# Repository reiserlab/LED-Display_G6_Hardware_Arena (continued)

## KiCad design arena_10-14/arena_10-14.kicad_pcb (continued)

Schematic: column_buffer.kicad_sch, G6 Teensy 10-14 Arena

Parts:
C44, C45, C46, C47: 0.1uF; C_0402_1005Metric; LCSC Part # C1525
R109, R110, R111, R112, R113, R114, R115, R116: 33; R_0402_1005Metric; LCSC Part # C25105
U42, U43, U44, U45: 74LVC2G17; SOT-23-6; LCSC Part # C7394037

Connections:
+3.3V: C44.1, C45.1, C46.1, C47.1, U42.5 (VCC), U43.5 (VCC), U44.5 (VCC), U45.5 (VCC); also elsewhere on the board
/Fan Out/PAN.CIPO_B0_P1: R109.2; also elsewhere on the board
/Fan Out/PAN.COPI_B0_P1: U43.3; also elsewhere on the board
/Fan Out/PAN.CS_00_P1: U42.3; also elsewhere on the board
/Fan Out/PAN.CS_01_P1: U44.1; also elsewhere on the board
/Fan Out/PAN.CS_02_P1: U44.3; also elsewhere on the board
/Fan Out/PAN.CS_03_P1: U45.1; also elsewhere on the board
/Fan Out/PAN.EINT_P1: U45.3; also elsewhere on the board
/Fan Out/PAN.SCK_B0_P1: U43.1; also elsewhere on the board
/Panels/Panel Column P1/Column Buffer/CIPO_IN: U42.1; also elsewhere on the board
/Panels/Panel Column P1/Column Buffer/COPI_OUT: R111.2; also elsewhere on the board
/Panels/Panel Column P1/Column Buffer/CS0_OUT: R112.2; also elsewhere on the board
/Panels/Panel Column P1/Column Buffer/CS1_OUT: R113.2; also elsewhere on the board
/Panels/Panel Column P1/Column Buffer/CS2_OUT: R114.2; also elsewhere on the board
/Panels/Panel Column P1/Column Buffer/CS_3OUT: R115.2; also elsewhere on the board
/Panels/Panel Column P1/Column Buffer/EINT_OUT: R116.2; also elsewhere on the board
/Panels/Panel Column P1/Column Buffer/SCK_OUT: R110.2; also elsewhere on the board
GND: C44.2, C45.2, C46.2, C47.2, U42.2 (GND), U43.2 (GND), U44.2 (GND), U45.2 (GND); also elsewhere on the board
unnamed: R109.1, U42.6
unnamed: R110.1, U43.6
unnamed: R111.1, U43.4
unnamed: R112.1, U42.4
unnamed: R113.1, U44.6
unnamed: R114.1, U44.4
unnamed: R115.1, U45.6
unnamed: R116.1, U45.4

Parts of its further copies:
C50, C51, C52, C53, C55, C56, C57, C58, C60, C61, C62, C63, C65, C66, C67, C68, C70, C71, C72, C73, C75, C76, C77, C78, C80, C81, C82, C83, C85, C86, C87, C88, C153, C154, C155, C156: 0.1uF; C_0402_1005Metric; LCSC Part # C1525
R117, R118, R119, R120, R121, R122, R123, R124, R125, R126, R127, R128, R129, R130, R131, R132, R133, R134, R135, R136, R137, R138, R139, R140, R141, R142, R143, R144, R145, R146, R147, R148, R149, R150, R151, R152, R153, R154, R155, R156, R157, R158, R159, R160, R161, R162, R163, R164, R165, R166, R167, R168, R169, R170, R171, R172, R173, R174, R175, R176, R177, R178, R179, R180, R241, R242, R243, R244, R245, R246, R247, R248: 33; R_0402_1005Metric; LCSC Part # C25105
U46, U47, U48, U49, U50, U51, U52, U53, U54, U55, U56, U57, U58, U59, U60, U61, U62, U63, U64, U65, U66, U67, U68, U69, U70, U71, U72, U73, U74, U75, U76, U77, U128, U129, U130, U131: 74LVC2G17; SOT-23-6; LCSC Part # C7394037

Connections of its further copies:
+3.3V: C50.1, C51.1, C52.1, C53.1, C55.1, C56.1, C57.1, C58.1, C60.1, C61.1, C62.1, C63.1, C65.1, C66.1, C67.1, C68.1, C70.1, C71.1, C72.1, C73.1, C75.1, C76.1, C77.1, C78.1, C80.1, C81.1, C82.1, C83.1, C85.1, C86.1, C87.1, C88.1, C153.1, C154.1, C155.1, C156.1, U46.5 (VCC), U47.5 (VCC), U48.5 (VCC), U49.5 (VCC), U50.5 (VCC), U51.5 (VCC), U52.5 (VCC), U53.5 (VCC), U54.5 (VCC), U55.5 (VCC), U56.5 (VCC), U57.5 (VCC), U58.5 (VCC), U59.5 (VCC), U60.5 (VCC), U61.5 (VCC), U62.5 (VCC), U63.5 (VCC), U64.5 (VCC), U65.5 (VCC), U66.5 (VCC), U67.5 (VCC), U68.5 (VCC), U69.5 (VCC), U70.5 (VCC), U71.5 (VCC), U72.5 (VCC), U73.5 (VCC), U74.5 (VCC), U75.5 (VCC), U76.5 (VCC), U77.5 (VCC), U128.5 (VCC), U129.5 (VCC), U130.5 (VCC), U131.5 (VCC); also elsewhere on the board
/Fan Out/PAN.CIPO_B0_P2: R117.2; also elsewhere on the board
/Fan Out/PAN.CIPO_B0_P3: R125.2; also elsewhere on the board
/Fan Out/PAN.CIPO_B0_P4: R133.2; also elsewhere on the board
/Fan Out/PAN.CIPO_B0_P5: R141.2; also elsewhere on the board
/Fan Out/PAN.CIPO_B1_P6: R241.2; also elsewhere on the board
/Fan Out/PAN.CIPO_B1_P7: R149.2; also elsewhere on the board
/Fan Out/PAN.CIPO_B1_P8: R157.2; also elsewhere on the board
/Fan Out/PAN.CIPO_B1_P9: R165.2; also elsewhere on the board
/Fan Out/PAN.CIPO_B1_P10: R173.2; also elsewhere on the board
/Fan Out/PAN.COPI_B0_P2: U47.3; also elsewhere on the board
/Fan Out/PAN.COPI_B0_P3: U51.3; also elsewhere on the board
/Fan Out/PAN.COPI_B0_P4: U55.3; also elsewhere on the board
/Fan Out/PAN.COPI_B0_P5: U59.3; also elsewhere on the board
/Fan Out/PAN.COPI_B1_P6: U129.3; also elsewhere on the board
/Fan Out/PAN.COPI_B1_P7: U63.3; also elsewhere on the board
/Fan Out/PAN.COPI_B1_P8: U67.3; also elsewhere on the board
/Fan Out/PAN.COPI_B1_P9: U71.3; also elsewhere on the board
/Fan Out/PAN.COPI_B1_P10: U75.3; also elsewhere on the board
/Fan Out/PAN.CS_00_P6: U128.3; also elsewhere on the board
/Fan Out/PAN.CS_01_P6: U130.1; also elsewhere on the board
/Fan Out/PAN.CS_02_P6: U130.3; also elsewhere on the board
/Fan Out/PAN.CS_03_P6: U131.1; also elsewhere on the board
/Fan Out/PAN.CS_04_P2: U46.3; also elsewhere on the board
/Fan Out/PAN.CS_04_P7: U62.3; also elsewhere on the board
/Fan Out/PAN.CS_05_P2: U48.1; also elsewhere on the board
/Fan Out/PAN.CS_05_P7: U64.1; also elsewhere on the board
/Fan Out/PAN.CS_06_P2: U48.3; also elsewhere on the board
/Fan Out/PAN.CS_06_P7: U64.3; also elsewhere on the board
/Fan Out/PAN.CS_07_P2: U49.1; also elsewhere on the board
/Fan Out/PAN.CS_07_P7: U65.1; also elsewhere on the board
/Fan Out/PAN.CS_08_P3: U50.3; also elsewhere on the board
/Fan Out/PAN.CS_08_P8: U66.3; also elsewhere on the board
/Fan Out/PAN.CS_09_P3: U52.1; also elsewhere on the board
/Fan Out/PAN.CS_09_P8: U68.1; also elsewhere on the board
/Fan Out/PAN.CS_10_P3: U52.3; also elsewhere on the board
/Fan Out/PAN.CS_10_P8: U68.3; also elsewhere on the board
/Fan Out/PAN.CS_11_P3: U53.1; also elsewhere on the board
/Fan Out/PAN.CS_11_P8: U69.1; also elsewhere on the board
/Fan Out/PAN.CS_12_P4: U54.3; also elsewhere on the board
/Fan Out/PAN.CS_12_P9: U70.3; also elsewhere on the board
/Fan Out/PAN.CS_13_P4: U56.1; also elsewhere on the board
/Fan Out/PAN.CS_13_P9: U72.1; also elsewhere on the board
/Fan Out/PAN.CS_14_P4: U56.3; also elsewhere on the board
/Fan Out/PAN.CS_14_P9: U72.3; also elsewhere on the board
/Fan Out/PAN.CS_15_P4: U57.1; also elsewhere on the board
/Fan Out/PAN.CS_15_P9: U73.1; also elsewhere on the board
/Fan Out/PAN.CS_16_P5: U58.3; also elsewhere on the board
/Fan Out/PAN.CS_16_P10: U74.3; also elsewhere on the board
/Fan Out/PAN.CS_17_P5: U60.1; also elsewhere on the board
/Fan Out/PAN.CS_17_P10: U76.1; also elsewhere on the board
/Fan Out/PAN.CS_18_P5: U60.3; also elsewhere on the board
/Fan Out/PAN.CS_18_P10: U76.3; also elsewhere on the board
/Fan Out/PAN.CS_19_P5: U61.1; also elsewhere on the board
/Fan Out/PAN.CS_19_P10: U77.1; also elsewhere on the board
/Fan Out/PAN.EINT_P2: U49.3; also elsewhere on the board
/Fan Out/PAN.EINT_P3: U53.3; also elsewhere on the board
/Fan Out/PAN.EINT_P4: U57.3; also elsewhere on the board
/Fan Out/PAN.EINT_P5: U61.3; also elsewhere on the board
/Fan Out/PAN.EINT_P6: U131.3; also elsewhere on the board
/Fan Out/PAN.EINT_P7: U65.3; also elsewhere on the board
/Fan Out/PAN.EINT_P8: U69.3; also elsewhere on the board
/Fan Out/PAN.EINT_P9: U73.3; also elsewhere on the board
/Fan Out/PAN.EINT_P10: U77.3; also elsewhere on the board
/Fan Out/PAN.SCK_B0_P2: U47.1; also elsewhere on the board
/Fan Out/PAN.SCK_B0_P3: U51.1; also elsewhere on the board
/Fan Out/PAN.SCK_B0_P4: U55.1; also elsewhere on the board
/Fan Out/PAN.SCK_B0_P5: U59.1; also elsewhere on the board
/Fan Out/PAN.SCK_B1_P6: U129.1; also elsewhere on the board
/Fan Out/PAN.SCK_B1_P7: U63.1; also elsewhere on the board
/Fan Out/PAN.SCK_B1_P8: U67.1; also elsewhere on the board
/Fan Out/PAN.SCK_B1_P9: U71.1; also elsewhere on the board
/Fan Out/PAN.SCK_B1_P10: U75.1; also elsewhere on the board
/Panels/Panel Column P2/Column Buffer/CIPO_IN: U46.1; also elsewhere on the board
/Panels/Panel Column P2/Column Buffer/COPI_OUT: R119.2; also elsewhere on the board
/Panels/Panel Column P2/Column Buffer/CS0_OUT: R120.2; also elsewhere on the board
/Panels/Panel Column P2/Column Buffer/CS1_OUT: R121.2; also elsewhere on the board
/Panels/Panel Column P2/Column Buffer/CS2_OUT: R122.2; also elsewhere on the board
/Panels/Panel Column P2/Column Buffer/CS_3OUT: R123.2; also elsewhere on the board
/Panels/Panel Column P2/Column Buffer/EINT_OUT: R124.2; also elsewhere on the board
/Panels/Panel Column P2/Column Buffer/SCK_OUT: R118.2; also elsewhere on the board
/Panels/Panel Column P3/Column Buffer/CIPO_IN: U50.1; also elsewhere on the board
/Panels/Panel Column P3/Column Buffer/COPI_OUT: R127.2; also elsewhere on the board
/Panels/Panel Column P3/Column Buffer/CS0_OUT: R128.2; also elsewhere on the board
/Panels/Panel Column P3/Column Buffer/CS1_OUT: R129.2; also elsewhere on the board
/Panels/Panel Column P3/Column Buffer/CS2_OUT: R130.2; also elsewhere on the board
/Panels/Panel Column P3/Column Buffer/CS_3OUT: R131.2; also elsewhere on the board
/Panels/Panel Column P3/Column Buffer/EINT_OUT: R132.2; also elsewhere on the board
/Panels/Panel Column P3/Column Buffer/SCK_OUT: R126.2; also elsewhere on the board
/Panels/Panel Column P4/Column Buffer/CIPO_IN: U54.1; also elsewhere on the board
/Panels/Panel Column P4/Column Buffer/COPI_OUT: R135.2; also elsewhere on the board
/Panels/Panel Column P4/Column Buffer/CS0_OUT: R136.2; also elsewhere on the board
/Panels/Panel Column P4/Column Buffer/CS1_OUT: R137.2; also elsewhere on the board
/Panels/Panel Column P4/Column Buffer/CS2_OUT: R138.2; also elsewhere on the board
/Panels/Panel Column P4/Column Buffer/CS_3OUT: R139.2; also elsewhere on the board
/Panels/Panel Column P4/Column Buffer/EINT_OUT: R140.2; also elsewhere on the board
/Panels/Panel Column P4/Column Buffer/SCK_OUT: R134.2; also elsewhere on the board
/Panels/Panel Column P5/Column Buffer/CIPO_IN: U58.1; also elsewhere on the board
/Panels/Panel Column P5/Column Buffer/COPI_OUT: R143.2; also elsewhere on the board
/Panels/Panel Column P5/Column Buffer/CS0_OUT: R144.2; also elsewhere on the board
/Panels/Panel Column P5/Column Buffer/CS1_OUT: R145.2; also elsewhere on the board
/Panels/Panel Column P5/Column Buffer/CS2_OUT: R146.2; also elsewhere on the board
/Panels/Panel Column P5/Column Buffer/CS_3OUT: R147.2; also elsewhere on the board
/Panels/Panel Column P5/Column Buffer/EINT_OUT: R148.2; also elsewhere on the board
/Panels/Panel Column P5/Column Buffer/SCK_OUT: R142.2; also elsewhere on the board
/Panels/Panel Column P6/Column Buffer/CIPO_IN: U128.1; also elsewhere on the board
/Panels/Panel Column P6/Column Buffer/COPI_OUT: R243.2; also elsewhere on the board
/Panels/Panel Column P6/Column Buffer/CS0_OUT: R244.2; also elsewhere on the board
/Panels/Panel Column P6/Column Buffer/CS1_OUT: R245.2; also elsewhere on the board
/Panels/Panel Column P6/Column Buffer/CS2_OUT: R246.2; also elsewhere on the board
/Panels/Panel Column P6/Column Buffer/CS_3OUT: R247.2; also elsewhere on the board
/Panels/Panel Column P6/Column Buffer/EINT_OUT: R248.2; also elsewhere on the board
/Panels/Panel Column P6/Column Buffer/SCK_OUT: R242.2; also elsewhere on the board
/Panels/Panel Column P7/Column Buffer/CIPO_IN: U62.1; also elsewhere on the board
/Panels/Panel Column P7/Column Buffer/COPI_OUT: R151.2; also elsewhere on the board
/Panels/Panel Column P7/Column Buffer/CS0_OUT: R152.2; also elsewhere on the board
/Panels/Panel Column P7/Column Buffer/CS1_OUT: R153.2; also elsewhere on the board
/Panels/Panel Column P7/Column Buffer/CS2_OUT: R154.2; also elsewhere on the board
/Panels/Panel Column P7/Column Buffer/CS_3OUT: R155.2; also elsewhere on the board
/Panels/Panel Column P7/Column Buffer/EINT_OUT: R156.2; also elsewhere on the board
/Panels/Panel Column P7/Column Buffer/SCK_OUT: R150.2; also elsewhere on the board
/Panels/Panel Column P8/Column Buffer/CIPO_IN: U66.1; also elsewhere on the board
/Panels/Panel Column P8/Column Buffer/COPI_OUT: R159.2; also elsewhere on the board
/Panels/Panel Column P8/Column Buffer/CS0_OUT: R160.2; also elsewhere on the board
/Panels/Panel Column P8/Column Buffer/CS1_OUT: R161.2; also elsewhere on the board
/Panels/Panel Column P8/Column Buffer/CS2_OUT: R162.2; also elsewhere on the board
/Panels/Panel Column P8/Column Buffer/CS_3OUT: R163.2; also elsewhere on the board
/Panels/Panel Column P8/Column Buffer/EINT_OUT: R164.2; also elsewhere on the board
/Panels/Panel Column P8/Column Buffer/SCK_OUT: R158.2; also elsewhere on the board
/Panels/Panel Column P9/Column Buffer/CIPO_IN: U70.1; also elsewhere on the board
/Panels/Panel Column P9/Column Buffer/COPI_OUT: R167.2; also elsewhere on the board
/Panels/Panel Column P9/Column Buffer/CS0_OUT: R168.2; also elsewhere on the board
/Panels/Panel Column P9/Column Buffer/CS1_OUT: R169.2; also elsewhere on the board
/Panels/Panel Column P9/Column Buffer/CS2_OUT: R170.2; also elsewhere on the board
/Panels/Panel Column P9/Column Buffer/CS_3OUT: R171.2; also elsewhere on the board
/Panels/Panel Column P9/Column Buffer/EINT_OUT: R172.2; also elsewhere on the board
/Panels/Panel Column P9/Column Buffer/SCK_OUT: R166.2; also elsewhere on the board
/Panels/Panel Column P10/Column Buffer/CIPO_IN: U74.1; also elsewhere on the board
/Panels/Panel Column P10/Column Buffer/COPI_OUT: R175.2; also elsewhere on the board
/Panels/Panel Column P10/Column Buffer/CS0_OUT: R176.2; also elsewhere on the board
/Panels/Panel Column P10/Column Buffer/CS1_OUT: R177.2; also elsewhere on the board
/Panels/Panel Column P10/Column Buffer/CS2_OUT: R178.2; also elsewhere on the board
/Panels/Panel Column P10/Column Buffer/CS_3OUT: R179.2; also elsewhere on the board
/Panels/Panel Column P10/Column Buffer/EINT_OUT: R180.2; also elsewhere on the board
/Panels/Panel Column P10/Column Buffer/SCK_OUT: R174.2; also elsewhere on the board
GND: C50.2, C51.2, C52.2, C53.2, C55.2, C56.2, C57.2, C58.2, C60.2, C61.2, C62.2, C63.2, C65.2, C66.2, C67.2, C68.2, C70.2, C71.2, C72.2, C73.2, C75.2, C76.2, C77.2, C78.2, C80.2, C81.2, C82.2, C83.2, C85.2, C86.2, C87.2, C88.2, C153.2, C154.2, C155.2, C156.2, U46.2 (GND), U47.2 (GND), U48.2 (GND), U49.2 (GND), U50.2 (GND), U51.2 (GND), U52.2 (GND), U53.2 (GND), U54.2 (GND), U55.2 (GND), U56.2 (GND), U57.2 (GND), U58.2 (GND), U59.2 (GND), U60.2 (GND), U61.2 (GND), U62.2 (GND), U63.2 (GND), U64.2 (GND), U65.2 (GND), U66.2 (GND), U67.2 (GND), U68.2 (GND), U69.2 (GND), U70.2 (GND), U71.2 (GND), U72.2 (GND), U73.2 (GND), U74.2 (GND), U75.2 (GND), U76.2 (GND), U77.2 (GND), U128.2 (GND), U129.2 (GND), U130.2 (GND), U131.2 (GND); also elsewhere on the board
unnamed: R117.1, U46.6
unnamed: R118.1, U47.6
unnamed: R119.1, U47.4
unnamed: R120.1, U46.4
unnamed: R121.1, U48.6
unnamed: R122.1, U48.4
unnamed: R123.1, U49.6
unnamed: R124.1, U49.4
unnamed: R125.1, U50.6
unnamed: R126.1, U51.6
unnamed: R127.1, U51.4
unnamed: R128.1, U50.4
unnamed: R129.1, U52.6
unnamed: R130.1, U52.4
unnamed: R131.1, U53.6
unnamed: R132.1, U53.4
unnamed: R133.1, U54.6
unnamed: R134.1, U55.6
unnamed: R135.1, U55.4
unnamed: R136.1, U54.4
unnamed: R137.1, U56.6
unnamed: R138.1, U56.4
unnamed: R139.1, U57.6
unnamed: R140.1, U57.4
unnamed: R141.1, U58.6
unnamed: R142.1, U59.6
unnamed: R143.1, U59.4
unnamed: R144.1, U58.4
unnamed: R145.1, U60.6
unnamed: R146.1, U60.4
unnamed: R147.1, U61.6
unnamed: R148.1, U61.4
unnamed: R149.1, U62.6
unnamed: R150.1, U63.6
unnamed: R151.1, U63.4
unnamed: R152.1, U62.4
unnamed: R153.1, U64.6
unnamed: R154.1, U64.4
unnamed: R155.1, U65.6
unnamed: R156.1, U65.4
unnamed: R157.1, U66.6
unnamed: R158.1, U67.6
unnamed: R159.1, U67.4
unnamed: R160.1, U66.4
unnamed: R161.1, U68.6
unnamed: R162.1, U68.4
unnamed: R163.1, U69.6
unnamed: R164.1, U69.4
unnamed: R165.1, U70.6
unnamed: R166.1, U71.6
unnamed: R167.1, U71.4
unnamed: R168.1, U70.4
unnamed: R169.1, U72.6
unnamed: R170.1, U72.4
unnamed: R171.1, U73.6
unnamed: R172.1, U73.4
unnamed: R173.1, U74.6
unnamed: R174.1, U75.6
unnamed: R175.1, U75.4
unnamed: R176.1, U74.4
unnamed: R177.1, U76.6
unnamed: R178.1, U76.4
unnamed: R179.1, U77.6
unnamed: R180.1, U77.4
unnamed: R241.1, U128.6
unnamed: R242.1, U129.6
unnamed: R243.1, U129.4
unnamed: R244.1, U128.4
unnamed: R245.1, U130.6
unnamed: R246.1, U130.4
unnamed: R247.1, U131.6
unnamed: R248.1, U131.4

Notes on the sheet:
SN74LVC1G125DRLR 296-18012-2-ND SN74HCS08BQAR 296-SN74HCS08BQARTR-ND

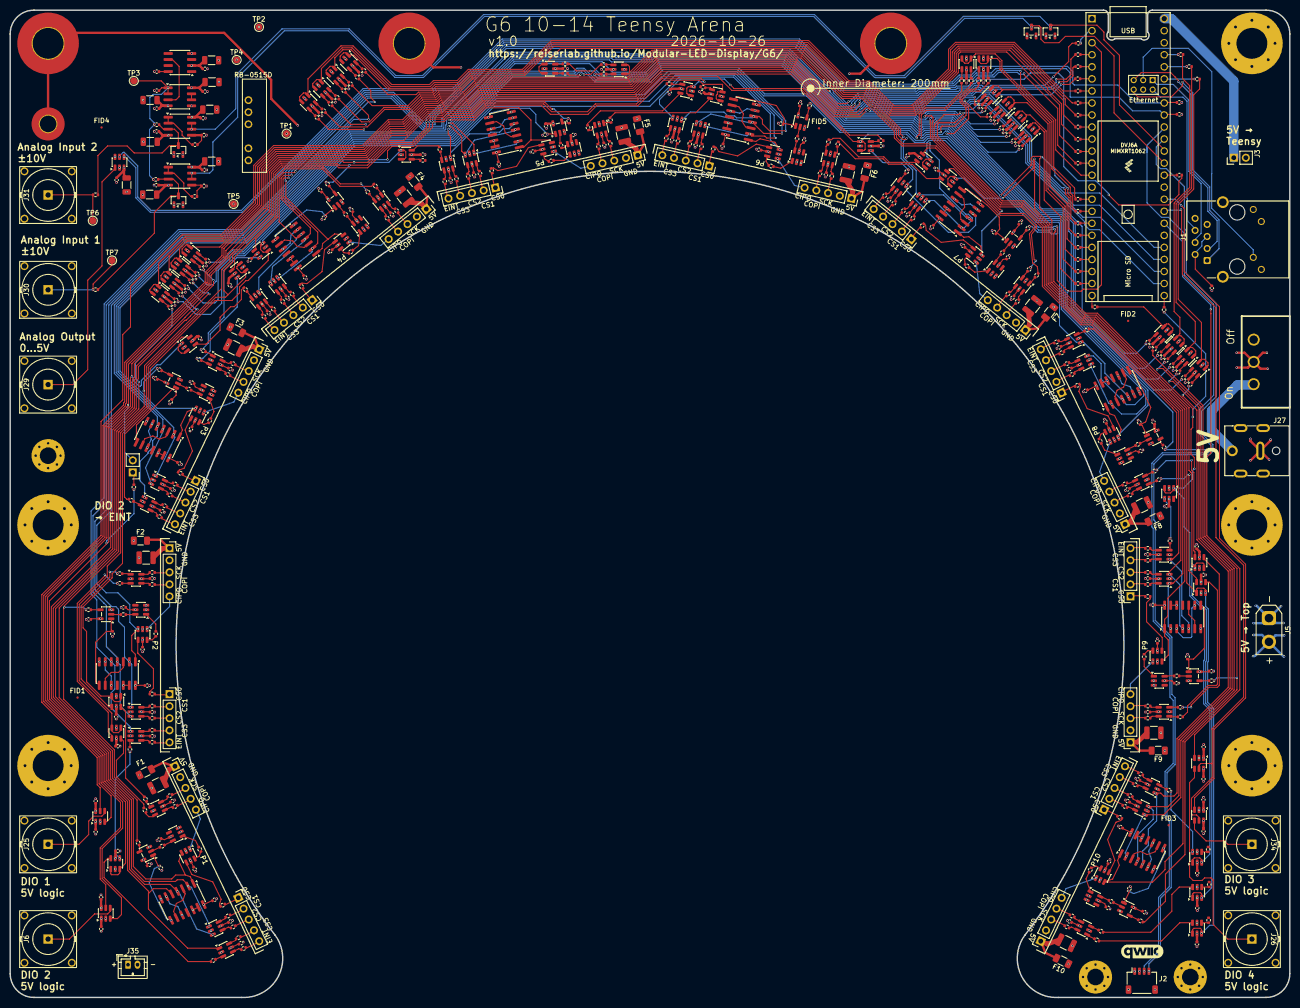
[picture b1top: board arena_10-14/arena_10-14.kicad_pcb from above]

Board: 6 copper layers, 270.0 x 208.3 mm, 571 parts (0 on the bottom side), 482 nets.

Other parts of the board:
H9, H11, H12: MountingHole_Pad; MountingHole_3.5mm_Pad_Via
H10: MountingHole_Pad; MountingHole_3.5mm_Pad_TopBottom

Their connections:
GND: H9.1 (1_1), H10.1 (1_1), H11.1 (1_1), H12.1 (1_1); also elsewhere on the board

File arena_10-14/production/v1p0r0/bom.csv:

Designator,Footprint,Quantity,Value,LCSC Part #
"C1, C10, C11, C112, C113, C114, C115, C116, C117, C118, C119, C12, C120, C121, C122, C123, C124, C125, C126, C127, C128, C129, C13, C130, C131, C132, C133, C134, C135, C136, C137, C138, C139, C14, C140, C141, C146, C147, C148, C15, C153, C154, C155, C156, C16, C17, C18, C19, C20, C21, C22, C23, C24, C25, C26, C27, C28, C29, C30, C31, C32, C33, C34, C35, C36, C37, C38, C39, C40, C41, C42, C43, C44, C45, C46, C47, C50, C51, C52, C53, C55, C56, C57, C58, C6, C60, C61, C62, C63, C65, C66, C67, C68, C7, C70, C71, C72, C73, C75, C76, C77, C78, C8, C80, C81, C82, C83, C85, C86, C87, C88, C89, C9, C90, C91, C92, C93, C96",0402,118,0.1uF,C1525
"C100, C101, C104, C105, C108, C109, C95, C97, C99",0402,9,100nF,C307331
"C102, C103, C106, C107, C110, C111, C94, C98",1206,8,10uF,C89632
"C152, C48, C49, C54, C59, C64, C69, C74, C79, C84",1210,10,100uF,C7432790
"D1, D2, D3, D4",SOT-23,4,BAS40-04,C7502688
"F1, F10, F2, F3, F4, F5, F6, F7, F8, F9",1206,10,1.1A PTC,C126818
J1,RJ45_Cetus_J1B1211CCD_Horizontal,1,Cetus RJ45 Magjack,C910371
"J10, J11, J12, J13, J14, J15, J16, J17, J18, J19, J20, J21, J22, J23, J24, J32, J33, J7, J8, J9",PinSocket_1x05_P2.54mm_Vertical,20,Conn_01x05,C50950
J2,JST_SH_SM04B-SRSS-TB_1x04-1MP_P1.00mm_Horizontal,1,Qwiic,C145956
"J25, J26, J29, J30, J31, J34, J6",BNC_HenryTech_HL-BNC_KHDA,7,Conn_Coaxial,C19712152
J27,DC-053D-20A,1,Barrel_Jack,C707274
"J3, J4",PinHeader_1x02_P2.54mm_Vertical,2,Conn_01x02,C124375
J35,JST_PH_B2B-PH-K_1x02_P2.00mm_Vertical,1,JST PH,C594142
J5,AMASS_XT30UPB-F_1x02_P5.0mm_Vertical,1,XT30,C108769
"R1, R10, R100, R101, R102, R103, R104, R105, R106, R107, R108, R109, R11, R110, R111, R112, R113, R114, R115, R116, R117, R118, R119, R12, R120, R121, R122, R123, R124, R125, R126, R127, R128, R129, R13, R130, R131, R132, R133, R134, R135, R136, R137, R138, R139, R14, R140, R141, R142, R143, R144, R145, R146, R147, R148, R149, R15, R150, R151, R152, R153, R154, R155, R156, R157, R158, R159, R16, R160, R161, R162, R163, R164, R165, R166, R167, R168, R169, R17, R170, R171, R172, R173, R174, R175, R176, R177, R178, R179, R18, R180, R19, R197, R199, R2, R20, R200, R202, R203, R205, R206, R208, R209, R21, R211, R212, R214, R215, R217, R218, R22, R220, R221, R223, R23, R235, R237, R24, R241, R242, R243, R244, R245, R246, R247, R248, R29, R3, R33, R34, R35, R36, R37, R38, R39, R4, R40, R41, R42, R43, R44, R45, R46, R47, R48, R49, R5, R50, R51, R52, R53, R54, R55, R56, R57, R58, R59, R6, R60, R61, R62, R63, R64, R65, R66, R67, R68, R69, R7, R70, R71, R72, R73, R74, R75, R76, R77, R78, R79, R8, R80, R81, R82, R83, R84, R85, R86, R87, R88, R89, R9, R90, R91, R92, R93, R94, R95, R96, R97, R98",0402,200,33,C25105
"R189, R190, R193, R196",0402,4,10k,C190095
"R191, R192",0402,2,20k,C705630
"R194, R195",0402,2,10k,C190095 
"R198, R201, R204, R207, R210, R213, R216, R219, R222, R236",0402,10,5k,C5948099
"R30, R31, R32",0402,3,1k,C11702
R99,0402,1,33,C25105
SW1,slide_switch,1,SW_SPDT,C19189125
"U10, U102, U105, U108, U11, U111, U114, U12, U124, U128, U129, U13, U130, U131, U14, U15, U16, U17, U18, U19, U20, U21, U22, U23, U24, U25, U26, U27, U28, U29, U30, U31, U32, U33, U34, U35, U36, U37, U38, U39, U4, U40, U41, U42, U43, U44, U45, U46, U47, U48, U49, U5, U50, U51, U52, U53, U54, U55, U56, U57, U58, U59, U6, U60, U61, U62, U63, U64, U65, U66, U67, U68, U69, U7, U70, U71, U72, U73, U74, U75, U76, U77, U8, U9, U90, U93, U96, U99",SOT-23-6,88,74LVC2G17,C7394037
"U100, U103, U106, U109, U112, U122, U88, U91, U94, U97",SOT-23-5,10,74LVC1G125,C7394017
"U101, U104, U107, U110, U113, U123, U89, U92, U95, U98",SOIC-14_3.9x8.7mm_P1.27mm,10,SN74HCS08,C2868021
"U3, U78, U79, U80",SOT-23-6,4,SN74LVC1T45DBV,C7843
"U83, U86, U87",SOIC-8_3.9x4.9mm_P1.27mm,3,OPA2277,C24460
U84,SOIC-8_3.9x4.9mm_P1.27mm,1,REF102AU,C81460
U85,SOT-23-6,1,MCP4725xxx-xCH,C144198
